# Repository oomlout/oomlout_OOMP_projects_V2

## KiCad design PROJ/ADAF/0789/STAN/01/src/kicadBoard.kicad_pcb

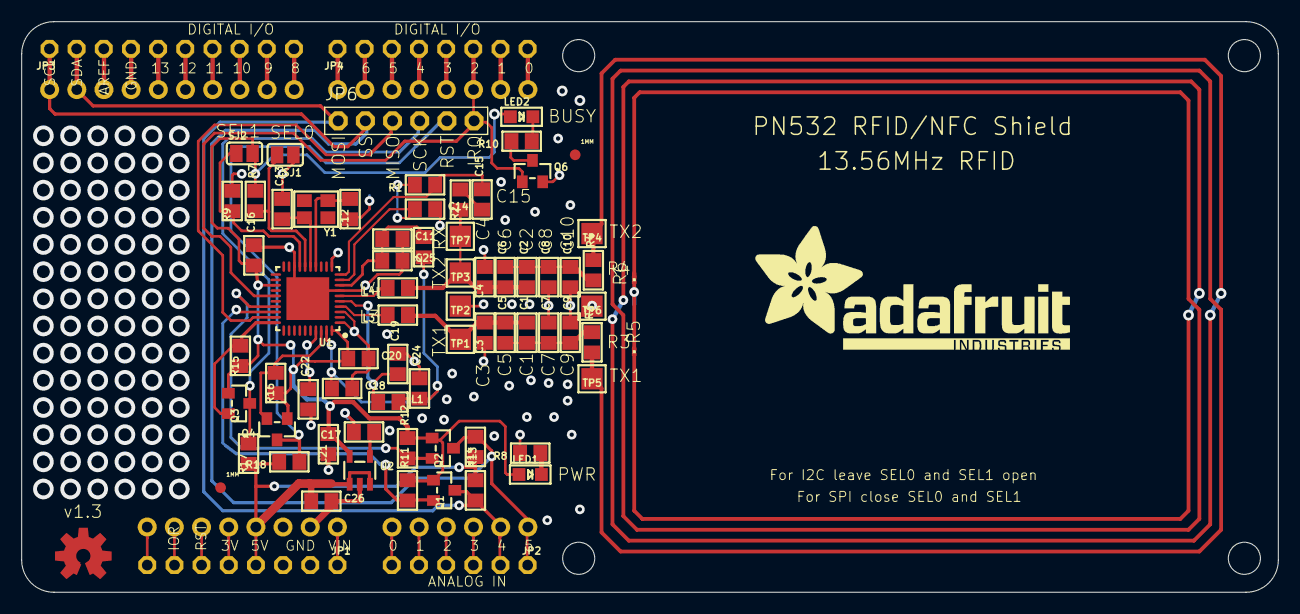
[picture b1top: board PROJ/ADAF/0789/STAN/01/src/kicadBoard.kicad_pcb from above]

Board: 2 copper layers, 117.5 x 53.3 mm, 80 parts (0 on the bottom side), 59 nets.

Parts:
@HOLE0, @HOLE1, @HOLE2, @HOLE3: (no value)
C1, C2: 22pF; 0805
C3, C4: 220pF; 0805
C5, C6, C9, C10: NC; 0805
C7, C8: 100pF; 0805
C11, C14, C16, C17, C20, C24: 0.1µF; 0805
C12, C13: 33pF; 0805
C15: 1000pF; 0805
C18, C19, C21, C22, C25, C26: 10µF; 0805
FID1, FID2: FIDUCIAL1X2.5; FIDUCIAL-1X2.5
JP1, JP4: 1X08_ROUND_70
JP2: 1X06_ROUND_70
JP3: 1X10_ROUND70
JP6: 1X06-BIG
L1, L2: FERRITE; 0805
L3, L4: 560nH; 0805
LED1: PWR; CHIPLED_0805
LED2: IRQ; CHIPLED_0805
Q1, Q2, Q3, Q4, Q6: BSS138; SOT23-WIDE
R1: 1.0K; 0805
R2: 1.69K; 0805
R3, R4: 1.5; 0805
R5, R6: NC; R0201
R7, R9, R11, R12, R13, R14, R15, R16, R17, R18: 10K; 0805
R8, R10: TBD; 0805
SJ1, SJ2: SOLDERJUMPER_REFLOW_NOPASTE
TP1: TX1_POST; TESTPOINT_PAD_2MM
TP2, TP6: TGND; TESTPOINT_PAD_2MM
TP3: TX2_POST; TESTPOINT_PAD_2MM
TP4: TX2_PRE; TESTPOINT_PAD_2MM
TP5: TX1_PRE; TESTPOINT_PAD_2MM
TP7: RX; TESTPOINT_PAD_2MM
U1: PN532; HVQFN40-6X6
U2: ADP122(3.3V); SOT23-5
U3: ARDUINOR3NODIM; ARDUINOR3-NODIM
U$3: ADAFRUIT_TEXT_30MM
U$50: OSHWLOGO_TOP_0.2
Y1: 27.12MHz; CRYSTAL_3.2X2.5

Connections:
5.0V: C26.1, JP1.4, R13.2, R14.2, R17.2, R18.2, U2.1, U2.3, U3.5V
GND: C3.2, C4.1, C7.2, C8.1, C9.2, C10.1, C11.2, C12.2, C13.2, C14.2, C16.2, C17.2, C18.2, C19.2, C20.2, C21.2, C22.1, C24.2, C25.2, C26.2, JP1.2, JP1.3, JP3.4, Q6.2, R5.2, R6.1, R8.2, R9.1, SJ1.1, TP2.P$1, TP6.P$1, U1.1, U1.3, U1.7, U1.11, U1.18, U1.TP, U2.2, U3.GND, U3.GND1, U3.GND2
IRQ: JP4.6, JP6.6, Q6.1, U1.25, U3.D2
MISO: JP6.3, U1.29
MOSI/SDA/TX: Q1.2, R11.1, U1.28
MOSI/SDA_5.0V: JP2.2, JP3.2, JP6.1, Q1.3, R13.1, U3.A4, U3.SDA
unnamed: L3.2, U1.4
unnamed: L4.2, U1.6
unnamed: C1.2, C3.1, C5.2, L3.1, TP1.P$1
unnamed: R3.1, R6.2, TP5.P$1
unnamed: R4.2, R5.1, TP4.P$1
unnamed: LED1.C, R8.1
unnamed: C12.1, U1.14, Y1.1
unnamed: C13.1, U1.15, Y1.2
unnamed: C15.1, R2.1
unnamed: C14.1, R1.2, U1.9
unnamed: C15.2, R1.1, U1.10
unnamed: C2.1, C4.2, C6.1, L4.1, R2.2, TP3.P$1, TP7.P$1
unnamed: C11.1, C25.1, L2.1, U1.8
unnamed: C19.1, L1.1, U1.5
unnamed: JP1.1, U3.VIN
unnamed: JP1.5, U3.3V
unnamed: JP1.6, U3.RESET
unnamed: JP1.7, U3.IOREF
unnamed: JP1.8, U3.RESERVED
unnamed: JP2.3, U3.A3
unnamed: JP2.4, U3.A2
unnamed: JP2.5, U3.A1
unnamed: JP2.6, U3.A0
unnamed: JP3.3, U3.AREF
unnamed: JP3.5, U3.D13
unnamed: JP3.6, U3.D12
unnamed: JP3.7, U3.D11
unnamed: JP3.8, U3.D10
unnamed: JP3.9, U3.D9
unnamed: JP3.10, U3.D8
unnamed: JP4.1, U3.D7
unnamed: JP4.2, U3.D6
unnamed: JP4.3, U3.D5
unnamed: JP4.4, U3.D4
unnamed: JP4.5, U3.D3
unnamed: LED2.C, R10.1
unnamed: JP4.7, U3.D1
unnamed: JP4.8, U3.D0
unnamed: Q6.3, R10.2
unnamed: C17.1, U2.4
unnamed: C22.2, U1.37
NSS/SCL/RX: Q2.2, R12.1, U1.27
NSS/SCL_5.0V: JP2.1, JP3.1, JP6.2, Q2.3, R14.1, U3.A5, U3.SCL
RSTPD_N: Q4.2, R16.1, U1.38
RSTPD_N_5.0V: JP6.5, Q4.3, R18.1
SCK: Q3.2, R15.1, U1.30
SCK_5.0V: JP6.4, Q3.3, R17.1
SEL0: R7.1, SJ1.2, U1.16
SEL1: R9.2, SJ2.1, U1.17
TX1_ANTENNA: C1.1, C5.1, C7.1, C9.1, R3.2
TX2_ANTENNA: C2.2, C6.2, C8.2, C10.2, R4.1
VCC: C18.1, C24.1, L1.2, L2.2, U1.39
VDD: C16.1, C20.1, C21.1, LED1.A, LED2.A, Q1.1, Q2.1, Q3.1, Q4.1, R7.2, R11.2, R12.2, R15.2, R16.2, SJ2.2, U1.23, U1.40, U2.5

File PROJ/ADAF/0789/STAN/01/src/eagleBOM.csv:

"Part";"Value";"Device";"Package";"Description";"BOM";
"C1";"22pF";"CAP_CERAMIC0805";"0805";"Ceramic Capacitors";"";
"C2";"22pF";"CAP_CERAMIC0805";"0805";"Ceramic Capacitors";"";
"C3";"220pF";"CAP_CERAMIC0805";"0805";"Ceramic Capacitors";"";
"C4";"220pF";"CAP_CERAMIC0805";"0805";"Ceramic Capacitors";"";
"C5";"NC";"CAP_CERAMIC0805";"0805";"Ceramic Capacitors";"";
"C6";"NC";"CAP_CERAMIC0805";"0805";"Ceramic Capacitors";"";
"C7";"100pF";"CAP_CERAMIC0805";"0805";"Ceramic Capacitors";"";
"C8";"100pF";"CAP_CERAMIC0805";"0805";"Ceramic Capacitors";"";
"C9";"NC";"CAP_CERAMIC0805";"0805";"Ceramic Capacitors";"";
"C10";"NC";"CAP_CERAMIC0805";"0805";"Ceramic Capacitors";"";
"C11";"0.1µF";"CAP_CERAMIC0805";"0805";"Ceramic Capacitors";"";
"C12";"33pF";"CAP_CERAMIC0805";"0805";"Ceramic Capacitors";"";
"C13";"33pF";"CAP_CERAMIC0805";"0805";"Ceramic Capacitors";"";
"C14";"0.1µF";"CAP_CERAMIC0805";"0805";"Ceramic Capacitors";"";
"C15";"1000pF";"CAP_CERAMIC0805";"0805";"Ceramic Capacitors";"";
"C16";"0.1µF";"CAP_CERAMIC0805";"0805";"Ceramic Capacitors";"";
"C17";"0.1µF";"CAP_CERAMIC0805";"0805";"Ceramic Capacitors";"";
"C18";"10µF";"CAP_CERAMIC0805";"0805";"Ceramic Capacitors";"";
"C19";"10µF";"CAP_CERAMIC0805";"0805";"Ceramic Capacitors";"";
"C20";"0.1µF";"CAP_CERAMIC0805";"0805";"Ceramic Capacitors";"";
"C21";"10µF";"CAP_CERAMIC0805";"0805";"Ceramic Capacitors";"";
"C22";"10µF";"CAP_CERAMIC0805";"0805";"Ceramic Capacitors";"";
"C24";"0.1µF";"CAP_CERAMIC0805";"0805";"Ceramic Capacitors";"";
"C25";"10µF";"CAP_CERAMIC0805";"0805";"Ceramic Capacitors";"";
"C26";"10µF";"CAP_CERAMIC0805";"0805";"Ceramic Capacitors";"";
"FID1";"FIDUCIAL1X2.5";"FIDUCIAL1X2.5";"FIDUCIAL-1X2.5";"Fiducial Alignment Points";"EXCLUDE";
"FID2";"FIDUCIAL1X2.5";"FIDUCIAL1X2.5";"FIDUCIAL-1X2.5";"Fiducial Alignment Points";"EXCLUDE";
"JP1";"";"HEADER-1X870MIL";"1X08_ROUND_70";"PIN HEADER";"";
"JP2";"";"HEADER-1X670MIL";"1X06_ROUND_70";"PIN HEADER";"";
"JP3";"";"HEADER-1X1070MIL";"1X10_ROUND70";"PIN HEADER";"";
"JP4";"";"HEADER-1X870MIL";"1X08_ROUND_70";"PIN HEADER";"";
"JP6";"";"PINHD-1X6B";"1X06-BIG";"PIN HEADER";"";
"L1";"FERRITE";"FERRITE0805";"0805";"Ferrite Bead";"";
"L2";"FERRITE";"FERRITE0805";"0805";"Ferrite Bead";"";
"L3";"560nH";"INDUCTOR0805";"0805";"Inductors";"";
"L4";"560nH";"INDUCTOR0805";"0805";"Inductors";"";
"LED1";"PWR";"LED0805";"CHIPLED_0805";"LED";"";
"LED2";"IRQ";"LED0805";"CHIPLED_0805";"LED";"";
"Q1";"BSS138";"MOSFET-NWIDE";"SOT23-WIDE";"N-Channel Mosfet";"";
"Q2";"BSS138";"MOSFET-NWIDE";"SOT23-WIDE";"N-Channel Mosfet";"";
"Q3";"BSS138";"MOSFET-NWIDE";"SOT23-WIDE";"N-Channel Mosfet";"";
"Q4";"BSS138";"MOSFET-NWIDE";"SOT23-WIDE";"N-Channel Mosfet";"";
"Q6";"BSS138";"MOSFET-NWIDE";"SOT23-WIDE";"N-Channel Mosfet";"";
"R1";"1.0K";"RESISTOR0805";"0805";"Resistors";"";
"R2";"1.69K";"RESISTOR0805";"0805";"Resistors";"";
"R3";"1.5";"RESISTOR0805";"0805";"Resistors";"";
"R4";"1.5";"RESISTOR0805";"0805";"Resistors";"";
"R5";"NC";"R-EU_R0201";"R0201";"RESISTOR, European symbol";"";
"R6";"NC";"R-EU_R0201";"R0201";"RESISTOR, European symbol";"";
"R7";"10K";"RESISTOR0805";"0805";"Resistors";"";
"R8";"TBD";"RESISTOR0805";"0805";"Resistors";"";
"R9";"10K";"RESISTOR0805";"0805";"Resistors";"";
"R10";"TBD";"RESISTOR0805";"0805";"Resistors";"";
"R11";"10K";"RESISTOR0805";"0805";"Resistors";"";
"R12";"10K";"RESISTOR0805";"0805";"Resistors";"";
"R13";"10K";"RESISTOR0805";"0805";"Resistors";"";
"R14";"10K";"RESISTOR0805";"0805";"Resistors";"";
"R15";"10K";"RESISTOR0805";"0805";"Resistors";"";
"R16";"10K";"RESISTOR0805";"0805";"Resistors";"";
"R17";"10K";"RESISTOR0805";"0805";"Resistors";"";
"R18";"10K";"RESISTOR0805";"0805";"Resistors";"";
"SJ1";"";"SOLDERJUMPERREFLOW_NOPASTE";"SOLDERJUMPER_REFLOW_NOPASTE";"SMD Solder JUMPER";"";
"SJ2";"";"SOLDERJUMPERREFLOW_NOPASTE";"SOLDERJUMPER_REFLOW_NOPASTE";"SMD Solder JUMPER";"";
"TP1";"TX1_POST";"TESTPOINTPAD";"TESTPOINT_PAD_2MM";"Test Point";"";
"TP2";"TGND";"TESTPOINTPAD";"TESTPOINT_PAD_2MM";"Test Point";"";
"TP3";"TX2_POST";"TESTPOINTPAD";"TESTPOINT_PAD_2MM";"Test Point";"";
"TP4";"TX2_PRE";"TESTPOINTPAD";"TESTPOINT_PAD_2MM";"Test Point";"";
"TP5";"TX1_PRE";"TESTPOINTPAD";"TESTPOINT_PAD_2MM";"Test Point";"";
"TP6";"TGND";"TESTPOINTPAD";"TESTPOINT_PAD_2MM";"Test Point";"";
"TP7";"RX";"TESTPOINTPAD";"TESTPOINT_PAD_2MM";"Test Point";"";
"U1";"PN532";"PN532";"HVQFN40-6X6";"PN532 - Near Field Communication (NFC) controller";"";
"U2";"ADP122(3.3V)";"VREG_SOT23-5";"SOT23-5";"SOT23-5 Fixed Voltage Regulators";"";
"U3";"ARDUINOR3NODIM";"ARDUINOR3NODIM";"ARDUINOR3-NODIM";"This is a new object for the new Arduino R3 - with extra pins that you may want to use (such as IOref, and duplicated A4/A5";"";
"Y1";"27.12MHz";"CRYSTAL3.2X2.5";"CRYSTAL_3.2X2.5";"Crystals";"";

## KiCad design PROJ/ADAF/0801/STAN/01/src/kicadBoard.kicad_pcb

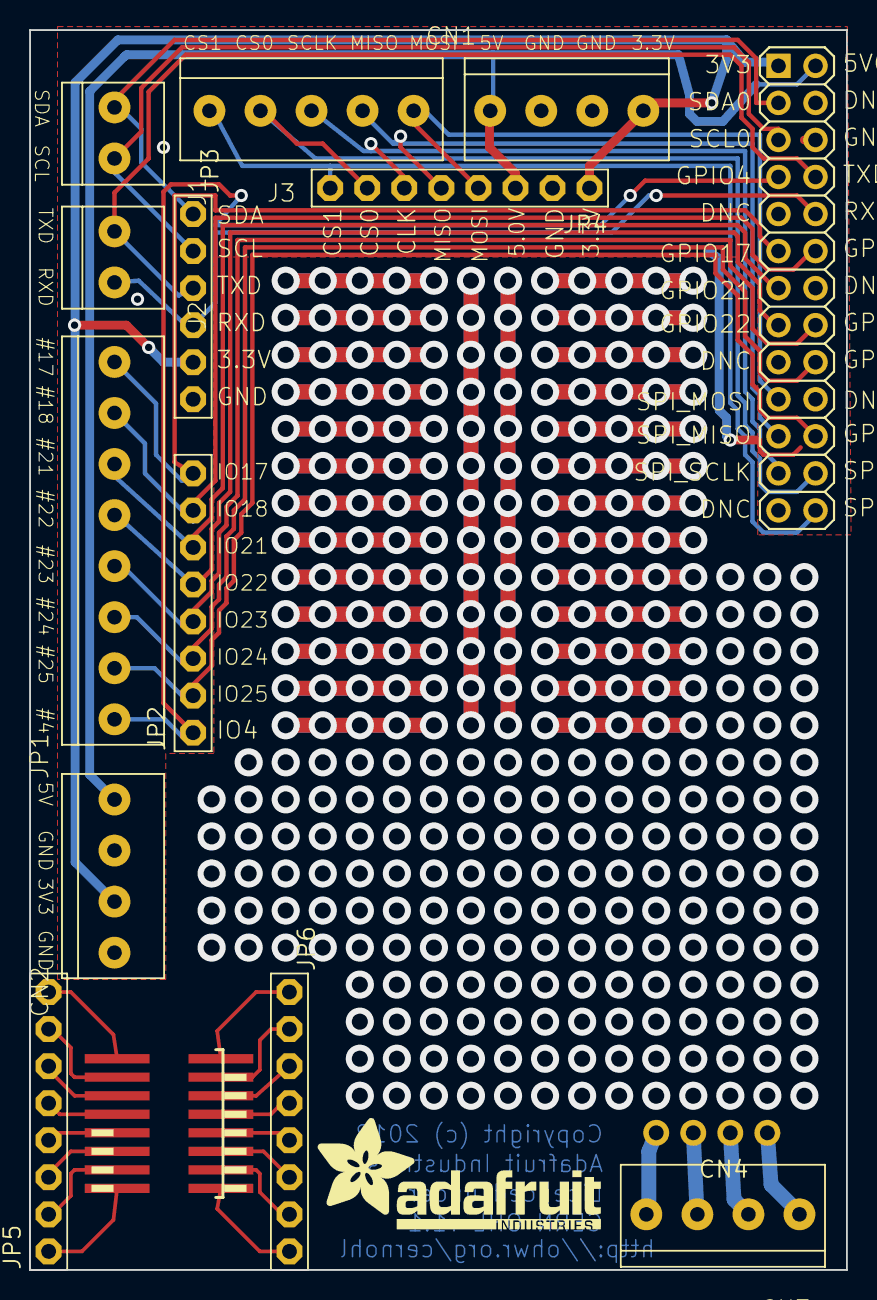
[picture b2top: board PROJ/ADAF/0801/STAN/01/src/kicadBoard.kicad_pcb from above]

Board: 16 copper layers, 56.0 x 85.0 mm, 16 parts (0 on the bottom side), 40 nets.

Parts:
CN1, CN2, CN3: 1X4-3.5MM; 1X04-3.5MM
CN4: 1X4-CLEANBIG; 1X04-CLEANBIG
J1, J2: 1X2-3.5MM
J3: 1X5; 1X05-3.5MM
JP1: 1X08-3.5MM
JP2, JP4, JP5, JP6: 1X08-BIG
JP3: 1X06-BIG
U$1: RASPBERRYPI_BB; RASBERRYPI_SHIELD
U$2: SMD-16SOIC; SO-16NMW
U$3: ADAFRUIT_TEXT_20MM

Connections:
3.3V: CN1.1, CN2.3, JP3.5, JP4.1, U$1.1
5.0V: CN1.4, CN2.1, JP4.3, U$1.2
GND: CN1.2, CN1.3, CN2.2, CN2.4, JP3.6, JP4.2, U$1.6
GPIO4: JP1.8, JP2.1, U$1.7
GPIO17: JP1.1, JP2.8, U$1.11
GPIO18: JP1.2, JP2.7, U$1.12
GPIO21: JP1.3, JP2.6, U$1.13
GPIO22: JP1.4, JP2.5, U$1.15
GPIO23: JP1.5, JP2.4, U$1.16
GPIO24: JP1.6, JP2.3, U$1.18
GPIO25: JP1.7, JP2.2, U$1.22
MISO: J3.4, JP4.5, U$1.21
MOSI: J3.5, JP4.4, U$1.19
unnamed: JP5.1, U$2.P$16
unnamed: JP5.2, U$2.P$15
unnamed: JP5.3, U$2.P$14
unnamed: JP5.4, U$2.P$13
unnamed: JP5.5, U$2.P$12
unnamed: JP5.6, U$2.P$11
unnamed: JP5.7, U$2.P$10
unnamed: JP5.8, U$2.P$9
unnamed: JP6.1, U$2.P$8
unnamed: JP6.2, U$2.P$7
unnamed: JP6.3, U$2.P$6
unnamed: JP6.4, U$2.P$5
unnamed: JP6.5, U$2.P$4
unnamed: JP6.6, U$2.P$3
unnamed: JP6.7, U$2.P$2
unnamed: JP6.8, U$2.P$1
unnamed: CN3.4, CN4.1
unnamed: CN3.3, CN4.2
unnamed: CN3.2, CN4.3
unnamed: CN3.1, CN4.4
RXD: J2.1, JP3.4, U$1.10
SCL: J1.1, JP3.2, U$1.5
SCLK: J3.3, JP4.6, U$1.23
SDA: J1.2, JP3.1, U$1.3
SPI_CE0: J3.2, JP4.7, U$1.24
SPI_CE1: J3.1, JP4.8, U$1.26
TXD: J2.2, JP3.3, U$1.8

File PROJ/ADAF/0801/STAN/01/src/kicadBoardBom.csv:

"Id";"Designator";"Package";"Quantity";"Designation";"Supplier and ref";
1;"CN1,CN2,CN3";"1X04-3.5MM";3;"1X4-3.5MM";;;
2;"J1,J2";"1X2-3.5MM";2;"1X2-3.5MM";;;
3;"CN4";"1X04-CLEANBIG";1;"1X4-CLEANBIG";;;
4;"U$2";"SO-16NMW";1;"SMD-16SOIC";;;
5;"JP2,JP4,JP6,JP5";"1X08-BIG";4;"";;;
6;"J3";"1X05-3.5MM";1;"1X5";;;
7;"U$3";"ADAFRUIT_TEXT_20MM";1;"";;;
8;"U$1";"RASBERRYPI_SHIELD";1;"RASPBERRYPI_BB";;;
9;"JP3";"1X06-BIG";1;"";;;
10;"JP1";"1X08-3.5MM";1;"";;;

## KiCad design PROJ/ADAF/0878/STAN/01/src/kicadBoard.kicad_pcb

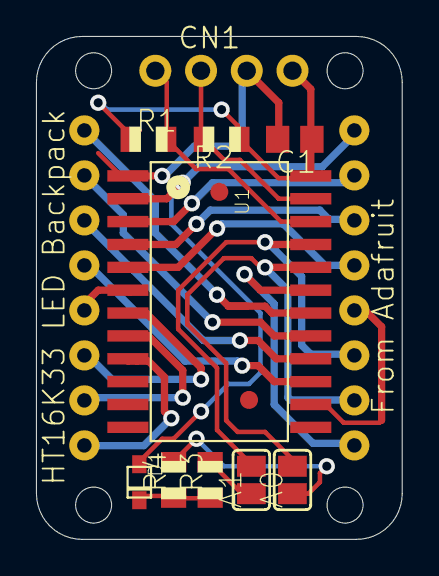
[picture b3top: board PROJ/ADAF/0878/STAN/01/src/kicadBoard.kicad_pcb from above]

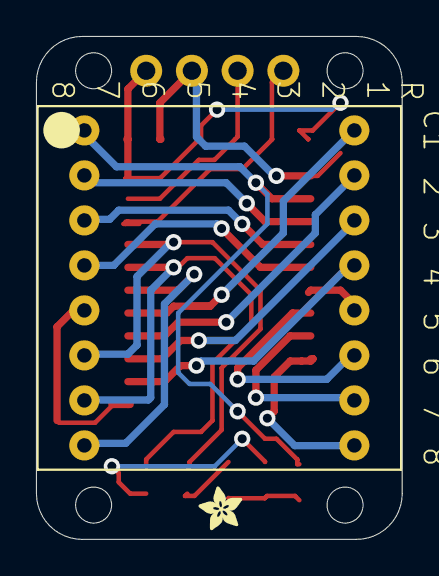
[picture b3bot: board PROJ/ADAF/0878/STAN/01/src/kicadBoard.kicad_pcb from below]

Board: 16 copper layers, 20.3 x 27.9 mm, 18 parts (2 on the bottom side), 23 nets.

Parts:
@HOLE0, @HOLE1, @HOLE2, @HOLE3: (no value)
A0, A1: SOLDERJUMPER_REFLOW_NOPASTE
C1: 10uF; C0805
CN1: 1X4-CLEANBIG; 1X04-CLEANBIG
D1: 1N4148; SOD-323F
LED1: BL-M07C881UR; SEGMENT_BL-M07C881UR
R1, R2, R3, R4: 10K; R0805
U1: SOP24_300MIL
U$1, U$2: FIDUCIAL; FIDUCIAL_1MM
U$4: ADAFRUIT_2.5MM

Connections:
A0: A0.2, LED1.7, U1.P$20
A1: A1.2, LED1.6, U1.P$21
GND: C1.2, CN1.3, U1.P$1
unnamed: LED1.9, U1.P$9
unnamed: LED1.10, U1.P$8
unnamed: LED1.11, U1.P$7
unnamed: LED1.12, U1.P$6
unnamed: LED1.4, U1.P$5
unnamed: LED1.3, U1.P$4
unnamed: LED1.2, U1.P$3
unnamed: D1.A, LED1.1, U1.P$2
unnamed: LED1.8, U1.P$19
unnamed: LED1.16, U1.P$18
unnamed: LED1.15, U1.P$17
unnamed: D1.C, R3.1, R4.1
unnamed: LED1.5, U1.P$14
unnamed: A1.1, R3.2
unnamed: A0.1, R4.2
SCL: CN1.1, R1.2, U1.P$22
SDA: CN1.2, R2.2, U1.P$23
SEG_F: LED1.14, U1.P$16
SEG_G: LED1.13, U1.P$15
VDD: C1.1, CN1.4, R1.1, R2.1, U1.P$24

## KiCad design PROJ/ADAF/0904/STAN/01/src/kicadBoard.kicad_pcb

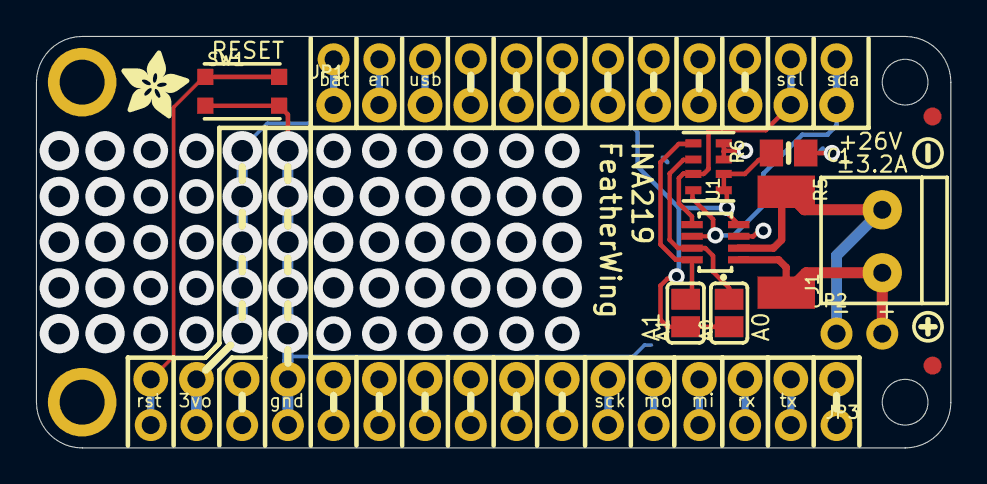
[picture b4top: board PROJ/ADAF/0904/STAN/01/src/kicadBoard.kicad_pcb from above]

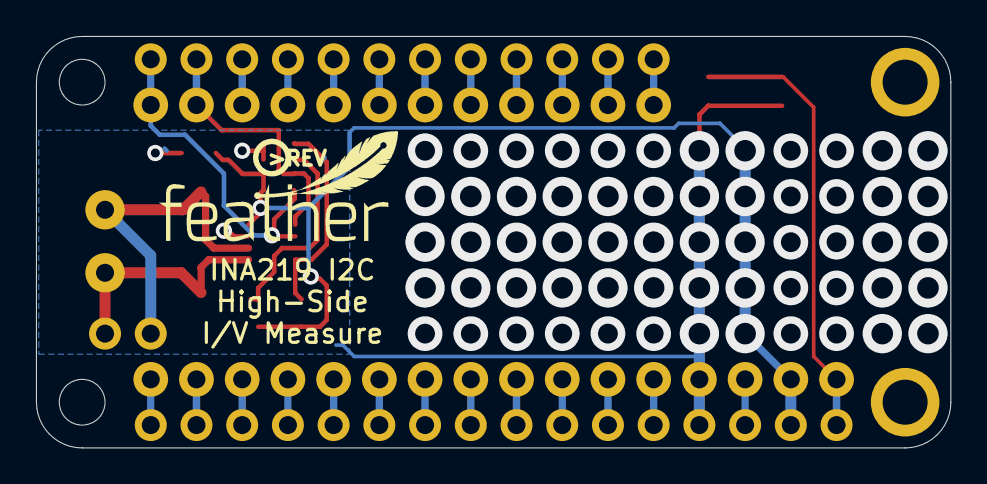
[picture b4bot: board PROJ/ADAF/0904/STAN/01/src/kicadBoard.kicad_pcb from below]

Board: 2 copper layers, 50.8 x 22.9 mm, 19 parts (2 on the bottom side), 32 nets.

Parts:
A0, A1: SOLDERJUMPER_REFLOW_NOPASTE
C1: 1uF; 0805-NO@1
FID1, FID2: FIDUCIAL_1MM
J1: 3.5mm; TERMBLOCK_1X2-3.5MM
JP1: 1X12_ROUND_76MIL
JP2: 1X02_ROUND
JP3: 1X16_ROUND_76MIL
MS1: FEATHERWING
R5: 0.1/1% (PT2512FK-070R1L); 2512
R6: 10K; RESPACK_4X0603
SW1: KMR2; BTN_KMR2_4.6X2.8
U1: INA219BIDCNT; SOT23-8
U$12: SYMBOL_PLUS
U$13: SYMBOL_MINUS
U$15: FEATHERLOGO_SMALL
U$16: ADAFRUIT_3.5MM
U$17: PCBFEAT-REV-040

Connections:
3.3V: A0.1, A1.1, C1.1, JP3.15, MS1.2, R6.5, R6.6, U1.4
A: JP3.12, MS1.5
AREF: JP3.14, MS1.3
B: JP3.11, MS1.6
C: JP3.10, MS1.7
D: JP3.9, MS1.8
E: JP3.8, MS1.9
EN: JP1.2, MS1.27
F: JP3.7, MS1.10
G: JP3.1, MS1.16
GND: C1.2, JP3.13, MS1.4, R6.7, R6.8, SW1.B, SW1.B', U1.3
H: JP1.10, MS1.19
I: JP1.9, MS1.20
J: JP1.8, MS1.21
K: JP1.7, MS1.22
L: JP1.6, MS1.23
M: JP1.5, MS1.24
MISO: JP3.4, MS1.13
MOSI: JP3.5, MS1.12
N: JP1.4, MS1.25
unnamed: A1.2, R6.1, U1.8
unnamed: A0.2, R6.2, U1.7
RESET: JP3.16, MS1.1, SW1.A, SW1.A'
RX: JP3.3, MS1.14
SCK: JP3.6, MS1.11
SCL: JP1.11, MS1.18, R6.3, U1.5
SDA: JP1.12, MS1.17, R6.4, U1.6
TX: JP3.2, MS1.15
USB: JP1.3, MS1.26
VBAT: JP1.1, MS1.28
VIN+: J1.2, JP2.2, R5.2, U1.1
VIN-: J1.1, JP2.1, R5.1, U1.2

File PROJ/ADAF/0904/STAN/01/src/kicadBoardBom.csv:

"Id";"Designator";"Package";"Quantity";"Designation";"Supplier and ref";
1;"R6";"RESPACK_4X0603";1;"10K";;;
2;"JP3";"1X16_ROUND_76MIL";1;"";;;
3;"U$12";"SYMBOL_PLUS";1;"";;;
4;"FID2,FID1";"FIDUCIAL_1MM";2;"FIDUCIAL_1MM";;;
5;"J1";"TERMBLOCK_1X2-3.5MM";1;"3.5mm";;;
6;"A1,A0";"SOLDERJUMPER_REFLOW_NOPASTE";2;"";;;
7;"C1";"0805-NO@1";1;"1uF";;;
8;"U1";"SOT23-8";1;"INA219BIDCNT";;;
9;"U$16";"ADAFRUIT_3.5MM";1;"";;;
10;"MS1";"FEATHERWING";1;"FEATHERWING";;;
11;"JP2";"1X02_ROUND";1;"";;;
12;"U$13";"SYMBOL_MINUS";1;"";;;
13;"R5";"2512";1;"0.1/1% (PT2512FK-070R1L)";;;
14;"JP1";"1X12_ROUND_76MIL";1;"";;;
15;"SW1";"BTN_KMR2_4.6X2.8";1;"KMR2";;;
16;"U$17";"PCBFEAT-REV-040";1;"";;;
17;"U$15";"FEATHERLOGO_SMALL";1;"";;;

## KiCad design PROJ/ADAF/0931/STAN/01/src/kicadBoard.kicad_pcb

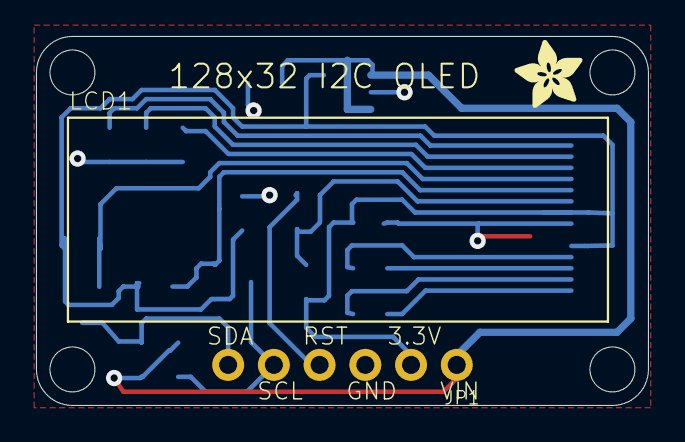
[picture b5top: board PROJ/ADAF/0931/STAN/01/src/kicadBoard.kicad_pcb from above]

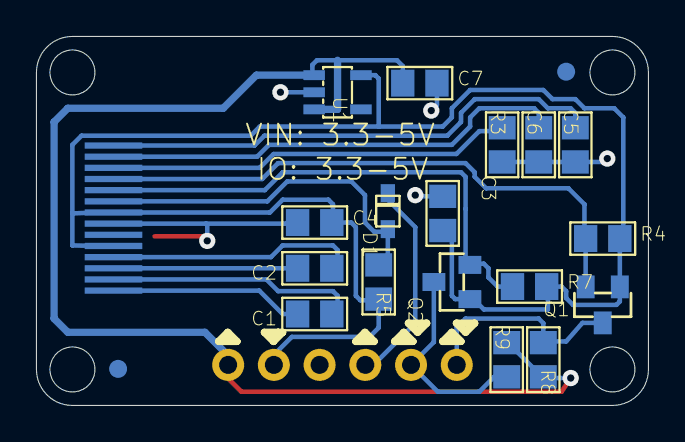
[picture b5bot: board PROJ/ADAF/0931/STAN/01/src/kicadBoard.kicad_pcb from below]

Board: 2 copper layers, 34.0 x 20.5 mm, 26 parts (19 on the bottom side), 16 nets.

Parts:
@HOLE0, @HOLE1, @HOLE2, @HOLE3: (no value)
C1, C2, C3, C4: 1uF; 0805
C5, C6, C7: 10uF; 0805
D1: 1N4148; SOD-323F
FID1, FID2: FIDUCIAL""; FIDUCIAL_1MM
JP1: 1X06_ROUND_70
LCD1: UG-2832HSWEG02_WRAPUNDER
Q1, Q2: BSS138; SOT23-WIDE
R3: 390K; 0805
R4, R5, R7, R8, R9: 10K; 0805
U1: RT9193; SOT23-5
U$16: ADAFRUIT_3.5MM

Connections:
3.3V: C3.2, C4.2, JP1.2, LCD1.5, LCD1.8, Q1.1, Q2.1, R4.2, R5.2, R7.2, U1.5
GND: C3.1, C4.1, C5.1, C6.1, C7.2, JP1.3, LCD1.7, R3.1, U1.2
unnamed: C1.2, LCD1.1
unnamed: C1.1, LCD1.2
unnamed: C2.2, LCD1.3
unnamed: C2.1, LCD1.4
unnamed: C6.2, LCD1.13
unnamed: C5.2, LCD1.14
unnamed: LCD1.12, R3.2
RES_3.3V: D1.A, LCD1.9, R5.1
RES_5.0V: D1.C, JP1.4
SCL_3.3V: LCD1.10, Q2.2, R7.1
SCL_5.0V: JP1.5, Q2.3, R9.1
SDA_3.3V: LCD1.11, Q1.2, R4.1
SDA_5.0V: JP1.6, Q1.3, R8.1
VIN: C7.1, JP1.1, R8.2, R9.2, U1.1, U1.3

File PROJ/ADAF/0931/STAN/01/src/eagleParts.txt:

Partlist

Exported from boardEagle.brd at 08/08/2022 09:35

EAGLE Version 9.6.2 Copyright (c) 1988-2020 Autodesk, Inc.

Assembly variant: 

Part     Value          Package                  Library      Position (inch)       Orientation

C1       1uF            0805                     microbuilder (0.73 0.2)            MR180
C2       1uF            0805                     microbuilder (0.73 0.3)            MR180
C3       1uF            0805                     microbuilder (0.45 0.42)           MR270
C4       1uF            0805                     microbuilder (0.73 0.4)            MR0
C5       10uF           0805                     microbuilder (0.16 0.57)           MR90
C6       10uF           0805                     microbuilder (0.24 0.57)           MR90
C7       10uF           0805                     microbuilder (0.5 0.705)           MR0
D1       1N4148         SOD-323F                 adafruit     (0.57 0.425)          MR90
FID1     FIDUCIAL""     FIDUCIAL_1MM             microbuilder (0.18 0.73)           MR0
FID2     FIDUCIAL""     FIDUCIAL_1MM             microbuilder (1.16 0.08)           MR0
JP1                     1X06_ROUND_70            microbuilder (0.66929134 0.08874016) R180
LCD1                    UG-2832HSWEG02_WRAPUNDER microbuilder (1.25 0.40984252)     R0
Q1       BSS138         SOT23-WIDE               microbuilder (0.1 0.22)            MR180
Q2       BSS138         SOT23-WIDE               microbuilder (0.43 0.27)           MR90
R3       390K           0805                     microbuilder (0.32 0.57)           MR90
R4       10K            0805                     microbuilder (0.1 0.365)           MR0
R5       10K            0805                     microbuilder (0.59 0.27)           MR270
R7       10K            0805                     microbuilder (0.26 0.26)           MR0
R8       10K            0805                     microbuilder (0.23 0.1)            MR270
R9       10K            0805                     microbuilder (0.31 0.1)            MR90
U1       RT9193         SOT23-5                  microbuilder (0.68 0.685)          MR270

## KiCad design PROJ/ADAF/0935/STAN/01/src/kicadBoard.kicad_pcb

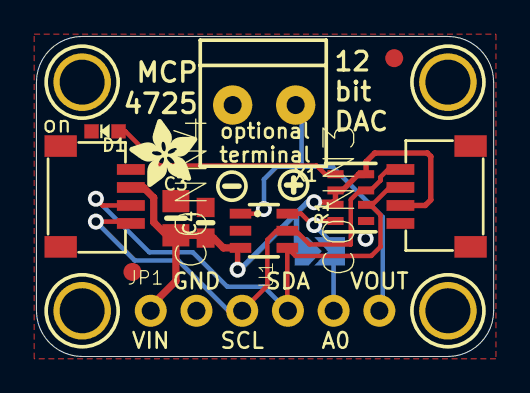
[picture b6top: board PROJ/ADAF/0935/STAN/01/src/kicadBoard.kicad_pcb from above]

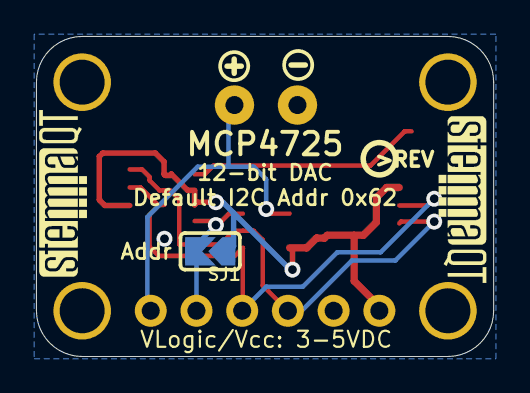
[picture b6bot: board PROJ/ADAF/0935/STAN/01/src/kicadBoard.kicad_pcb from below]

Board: 2 copper layers, 25.4 x 17.8 mm, 24 parts (6 on the bottom side), 7 nets.

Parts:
C3: 10uF; 0805-NO
C4: 0.1uF; 0603-NO
CONN3, CONN4: STEMMA_I2C_QT; JST_SH4
D1: GREEN; CHIPLED_0603_NOOUTLINE
FID3, FID4: FIDUCIAL_1MM
JP1: 1X06_ROUND_70
R1: 10K; RESPACK_4X0603
SJ1: SOLDERJUMPER_ARROW_NOPASTE
U1: MCP4725A1T-E/CH; SOT23-6
U$2, U$7: SYMBOL_PLUS
U$4, U$5: SYMBOL_MINUS
U$8: PCBFEAT-REV-040
U$20, U$21, U$25, U$27: MOUNTINGHOLE2.5; MOUNTINGHOLE_2.5_PLATED
U$29: ADAFRUIT_3.5MM
U$31, U$32: STEMMAQT
X1: 3.5mm Terminal Block; TERMBLOCK_1X2-3.5MM

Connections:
A0: JP1.5, R1.8, SJ1.2, U1.6
GND: C3.2, C4.2, CONN3.1, CONN3.MT1, CONN3.MT2, CONN4.1, CONN4.MT1, CONN4.MT2, D1.C, JP1.2, R1.1, U1.2, X1.1
unnamed: D1.A, R1.5
SCL: CONN3.4, CONN4.4, JP1.3, R1.3, U1.5
SDA: CONN3.3, CONN4.3, JP1.4, R1.2, U1.4
VCC: C3.1, C4.1, CONN3.2, CONN4.2, JP1.1, R1.4, R1.6, R1.7, SJ1.1, U1.3
VOUT: JP1.6, U1.1, X1.2

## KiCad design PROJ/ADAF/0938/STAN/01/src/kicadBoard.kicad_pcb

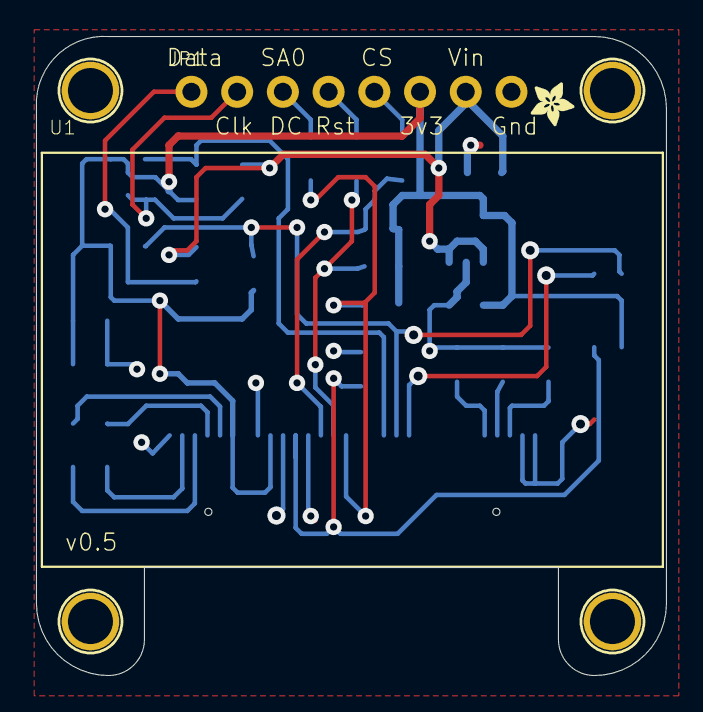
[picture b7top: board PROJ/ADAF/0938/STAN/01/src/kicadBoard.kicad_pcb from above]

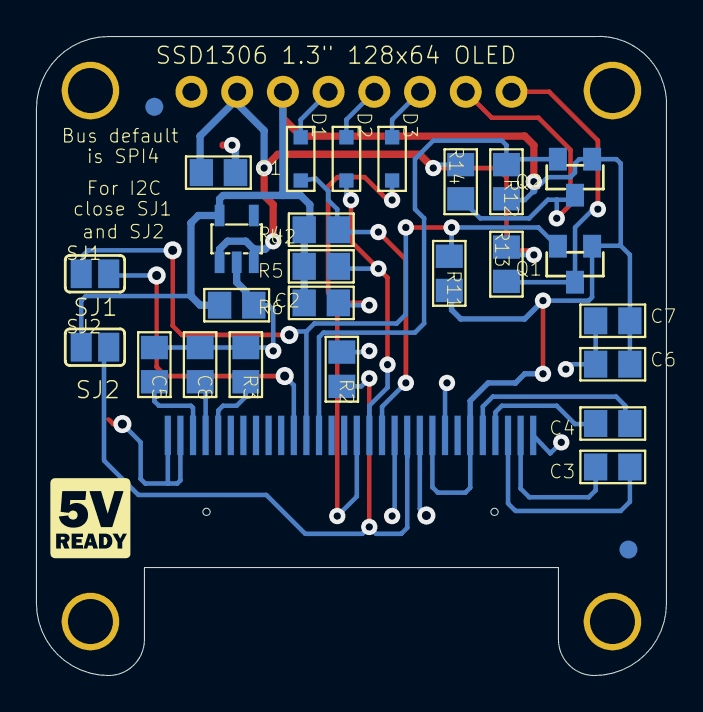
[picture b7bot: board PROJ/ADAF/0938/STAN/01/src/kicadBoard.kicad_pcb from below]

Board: 2 copper layers, 35.0 x 35.5 mm, 35 parts (28 on the bottom side), 22 nets.

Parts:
C1, C2, C5: 10uF; 0805
C3, C4, C6, C7, C8: 2.2uF; 0805
D1, D2, D3: 1N4148; SOD-323
FID1, FID2: FIDUCIAL""; FIDUCIAL_1MM
JP1: 1X08_ROUND_70
Q1, Q2: BSS138; SOT23-WIDE
R2, R4, R5, R6, R11, R12, R13, R14: 10K; 0805
R3: 390K; 0805
SJ1, SJ2: SOLDERJUMPER_REFLOW_NOPASTE
U1: UG-2864HSWEG01; UG-2864HSWEG01_1.3_WRAPAROUND
U2: SOT23-5
U$23, U$24, U$25, U$26: MOUNTINGHOLE2.5; MOUNTINGHOLE_2.5_PLATED
U$27: ADAFRUIT_2.5MM
U$28: LOGIC_5VREADY_5MM

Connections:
3.3V: C2.1, C6.2, C7.2, JP1.6, Q1.1, Q2.1, R4.2, R5.2, R6.2, R11.2, R12.2, SJ2.1, U1.6, U1.9, U2.5
CS_3.3V: D1.A, R4.1, U1.13
CS_5.0V: D1.C, JP1.5
D0/SCLK/SCK_3.3V: Q2.2, R12.1, U1.18
D0/SCLK/SCK_5.0V: JP1.2, Q2.3, R14.1
D1/MOSI/SDA1_3.3V: Q1.2, R11.1, SJ1.1, U1.19
D1/MOSI/SDA_5.0V: JP1.1, Q1.3, R13.1
DC/SA0_3.3V: D3.A, R6.1, U1.15
DC/SA0_5.0V: D3.C, JP1.3
GND: C1.2, C2.2, C5.1, C6.1, C7.1, C8.1, JP1.8, R2.1, R3.1, U1.1, U1.8, U1.10, U1.12, U1.29, U1.30, U2.2
unnamed: R2.2, SJ2.2, U1.11
unnamed: SJ1.2, U1.20
unnamed: R3.2, U1.26
unnamed: C3.2, U1.2
unnamed: C3.1, U1.3
unnamed: C4.2, U1.4
unnamed: C4.1, U1.5
unnamed: C5.2, U1.28
unnamed: C8.2, U1.27
RST_3.3V: D2.A, R5.1, U1.14
RST_5.0V: D2.C, JP1.4
VIN: C1.1, JP1.7, R13.2, R14.2, U2.1, U2.3

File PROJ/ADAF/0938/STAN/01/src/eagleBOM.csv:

"Part";"Value";"Device";"Package";"Description";"";
"C1";"10uF";"CAP_CERAMIC0805";"0805";"Ceramic Capacitors";"";
"C2";"10uF";"CAP_CERAMIC0805";"0805";"Ceramic Capacitors";"";
"C3";"2.2uF";"CAP_CERAMIC0805";"0805";"Ceramic Capacitors";"";
"C4";"2.2uF";"CAP_CERAMIC0805";"0805";"Ceramic Capacitors";"";
"C5";"10uF";"CAP_CERAMIC0805";"0805";"Ceramic Capacitors";"";
"C6";"2.2uF";"CAP_CERAMIC0805";"0805";"Ceramic Capacitors";"";
"C7";"2.2uF";"CAP_CERAMIC0805";"0805";"Ceramic Capacitors";"";
"C8";"2.2uF";"CAP_CERAMIC0805";"0805";"Ceramic Capacitors";"";
"D1";"1N4148";"DIODESOD-323";"SOD-323";"Diode";"";
"D2";"1N4148";"DIODESOD-323";"SOD-323";"Diode";"";
"D3";"1N4148";"DIODESOD-323";"SOD-323";"Diode";"";
"FID1";"FIDUCIAL""";"FIDUCIAL""";"FIDUCIAL_1MM";"Fiducial Alignment Points";"";
"FID2";"FIDUCIAL""";"FIDUCIAL""";"FIDUCIAL_1MM";"Fiducial Alignment Points";"";
"JP1";"";"HEADER-1X870MIL";"1X08_ROUND_70";"PIN HEADER";"";
"Q1";"BSS138";"MOSFET-NWIDE";"SOT23-WIDE";"N-Channel Mosfet";"";
"Q2";"BSS138";"MOSFET-NWIDE";"SOT23-WIDE";"N-Channel Mosfet";"";
"R2";"10K";"RESISTOR0805";"0805";"Resistors";"";
"R3";"390K";"RESISTOR0805";"0805";"Resistors";"";
"R4";"10K";"RESISTOR0805";"0805";"Resistors";"";
"R5";"10K";"RESISTOR0805";"0805";"Resistors";"";
"R6";"10K";"RESISTOR0805";"0805";"Resistors";"";
"R11";"10K";"RESISTOR0805";"0805";"Resistors";"";
"R12";"10K";"RESISTOR0805";"0805";"Resistors";"";
"R13";"10K";"RESISTOR0805";"0805";"Resistors";"";
"R14";"10K";"RESISTOR0805";"0805";"Resistors";"";
"SJ1";"";"SOLDERJUMPERREFLOW_NOPASTE";"SOLDERJUMPER_REFLOW_NOPASTE";"SMD Solder JUMPER";"";
"SJ2";"";"SOLDERJUMPERREFLOW_NOPASTE";"SOLDERJUMPER_REFLOW_NOPASTE";"SMD Solder JUMPER";"";
"U$23";"MOUNTINGHOLE2.5";"MOUNTINGHOLE2.5";"MOUNTINGHOLE_2.5_PLATED";"Mounting Hole";"";
"U$24";"MOUNTINGHOLE2.5";"MOUNTINGHOLE2.5";"MOUNTINGHOLE_2.5_PLATED";"Mounting Hole";"";
"U$25";"MOUNTINGHOLE2.5";"MOUNTINGHOLE2.5";"MOUNTINGHOLE_2.5_PLATED";"Mounting Hole";"";
"U$26";"MOUNTINGHOLE2.5";"MOUNTINGHOLE2.5";"MOUNTINGHOLE_2.5_PLATED";"Mounting Hole";"";
"U1";"UG-2864HSWEG01";"DISP_OLED_UG-2864HSWEG01";"UG-2864HSWEG01_1.3_WRAPAROUND";"UG-2864HSWEG01 OLED display";"";
"U2";"";"VREG_SOT23-5";"SOT23-5";"SOT23-5 Fixed Voltage Regulators";"";

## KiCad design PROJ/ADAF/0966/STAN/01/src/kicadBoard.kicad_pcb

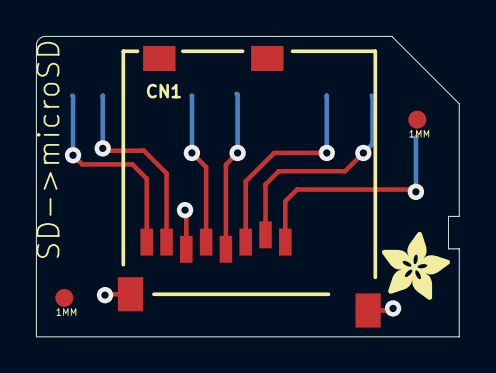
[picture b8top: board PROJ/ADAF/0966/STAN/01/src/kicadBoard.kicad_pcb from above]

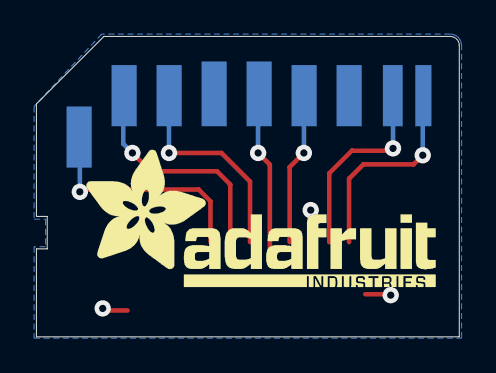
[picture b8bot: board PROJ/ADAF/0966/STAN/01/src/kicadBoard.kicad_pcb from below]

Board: 2 copper layers, 23.5 x 16.7 mm, 6 parts (2 on the bottom side), 8 nets.

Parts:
CN1: MICROSD
FID1, FID2: FIDUCIAL1X2.5; FIDUCIAL-1X2.5
U$2: SDCARD_PCBCARRIERTDOCU; SDCARD_PCBCARRIER_DOCU
U$5: ADAFRUIT_3.5MM
U$6: ADAFRUIT_TEXT_20MM

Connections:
CD/DAT3: CN1.2, U$2.P$1
CLK: CN1.5, U$2.P$5
CMD: CN1.3, U$2.P$2
DAT0: CN1.7, U$2.P$7
DAT1: CN1.8, U$2.P$8
DAT2: CN1.1, U$2.P$9
GND: CN1.6, CN1.MT1, CN1.MT2, U$2.P$3, U$2.P$6
VDD: CN1.4, U$2.P$4

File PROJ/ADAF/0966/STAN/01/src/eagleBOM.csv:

"Part";"Value";"Device";"Package";"Description";"";
"CN1";"";"MICROSD";"MICROSD";"MicroSD/Transflash Card Holder with SPI pinout";"";
"FID1";"FIDUCIAL1X2.5";"FIDUCIAL1X2.5";"FIDUCIAL-1X2.5";"Fiducial Alignment Points";"";
"FID2";"FIDUCIAL1X2.5";"FIDUCIAL1X2.5";"FIDUCIAL-1X2.5";"Fiducial Alignment Points";"";
"U$2";"SDCARD_PCBCARRIERTDOCU";"SDCARD_PCBCARRIERTDOCU";"SDCARD_PCBCARRIER_DOCU";"Physical PCB representing an SD Card";"";

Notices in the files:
PROJ/ADAF/0801/STAN/01/src/kicadBoard.kicad_pcb:
Copyright (c) 2012
Licenced under
B.Cu
CERN OHL v1.1
